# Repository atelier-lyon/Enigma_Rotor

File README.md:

# Enigma Rotor

## By Florian "FloRide" Reimat

## About

This repo is the Rotor panel PCB of the Enigma project

## Images:

### Schematic:

### PCB:

|               Front                |               Bottom               |
| :--------------------------------: | :--------------------------------: |
|  |  |

### 3D:

|                 Front                  |                Bottom                |
| :------------------------------------: | :----------------------------------: |
|    |  |
|                Tilted 1                |               Tilted 2               |
|  |   |

## Others:

- [Interactive BOM](Export/ibom/Engima_Rotor-ibom.html)
- [BOM](Export/bom/Engima_Rotor-bom.csv)
- [Cost](Export/cost/Engima_Rotor-kicost.xlsx)

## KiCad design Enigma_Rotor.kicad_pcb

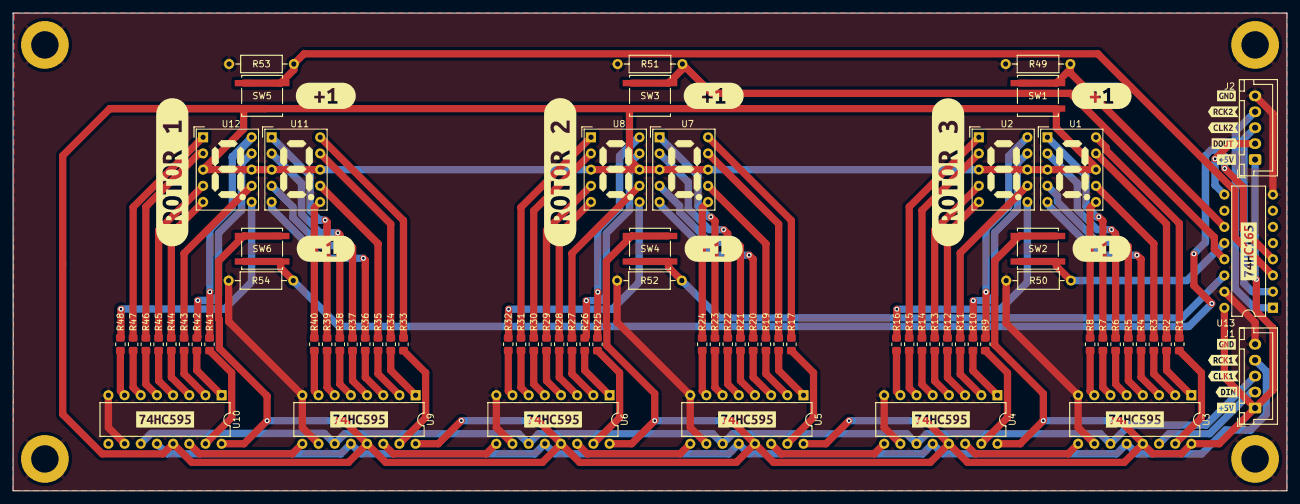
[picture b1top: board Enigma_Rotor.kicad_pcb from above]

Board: 2 copper layers, 200.0 x 75.0 mm, 105 parts (0 on the bottom side), 115 nets.

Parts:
H1, H2, H3, H4: MountingHole_Pad; MountingHole_4.3mm_M4_DIN965_Pad
J1, J2: Conn_01x05; JST_XH_B5B-XH-A_1x05_P2.50mm_Vertical
R1, R2, R3, R4, R5, R6, R7, R8, R9, R10, R11, R12, R13, R14, R15, R16, R17, R18, R19, R20, R21, R22, R23, R24, R25, R26, R27, R28, R29, R30, R31, R32, R33, R34, R35, R36, R37, R38, R39, R40, R41, R42, R43, R44, R45, R46, R47, R48: 155; R_0805_2012Metric_Pad1.20x1.40mm_HandSolder
R49, R50, R51, R52, R53, R54: 10k; R_Axial_DIN0207_L6.3mm_D2.5mm_P10.16mm_Horizontal
SW1, SW2, SW3, SW4, SW5, SW6: SW_Push_Dual; SW_Push_1P1T_NO_CK_KSC6xxJ
U1, U2, U7, U8, U11, U12: HDSP-561E
U3, U4, U5, U6, U9, U10: 74HC595; DIP-16_W7.62mm
U13: 74HC165; DIP-16_W7.62mm
kibuzzard-63728A6D: G***; kibuzzard-63728A6D
kibuzzard-63728A42: G***; kibuzzard-63728A42
kibuzzard-63728A55: G***; kibuzzard-63728A55
kibuzzard-63728A60: G***; kibuzzard-63728A60
kibuzzard-63728A71: G***; kibuzzard-63728A71
kibuzzard-637289C5: G***; kibuzzard-637289C5
kibuzzard-637289FA, kibuzzard-637289FA#2: G***; kibuzzard-637289FA
kibuzzard-6372869D, kibuzzard-6372869D#2, kibuzzard-6372869D#3: G***; kibuzzard-6372869D
kibuzzard-6372875B: G***; kibuzzard-6372875B
kibuzzard-6372894E: G***; kibuzzard-6372894E
kibuzzard-63728640, kibuzzard-63728640#2, kibuzzard-63728640#3: G***; kibuzzard-63728640
kibuzzard-63728741, kibuzzard-63728741#2, kibuzzard-63728741#3, kibuzzard-63728741#4, kibuzzard-63728741#5, kibuzzard-63728741#6: G***; kibuzzard-63728741
kibuzzard-63728829: G***; kibuzzard-63728829
kibuzzard-63728953: G***; kibuzzard-63728953
kibuzzard-63728972, kibuzzard-63728972#2: G***; kibuzzard-63728972

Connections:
+5V: J1.1, J2.1, SW1.1, SW2.1, SW3.1, SW4.1, SW5.1, SW6.1, U1.3 (CA), U1.8 (CA), U2.3 (CA), U2.8 (CA), U3.13 (~OE), U3.16 (VCC), U4.13 (~OE), U4.16 (VCC), U5.13 (~OE), U5.16 (VCC), U6.13 (~OE), U6.16 (VCC), U7.3 (CA), U7.8 (CA), U8.3 (CA), U8.8 (CA), U9.13 (~OE), U9.16 (VCC), U10.13 (~OE), U10.16 (VCC), U11.3 (CA), U11.8 (CA), U12.3 (CA), U12.8 (CA), U13.16 (VCC)
/ROTOR_1_DOWN: R50.1, SW2.2, U13.12 (D1)
/ROTOR_1_UP: R49.1, SW1.2, U13.11 (D0)
/ROTOR_2_DOWN: R52.1, SW4.2, U13.14 (D3)
/ROTOR_2_UP: R51.1, SW3.2, U13.13 (D2)
/ROTOR_3_DOWN: R54.1, SW6.2, U13.4 (D5)
/ROTOR_3_UP: R53.1, SW5.2, U13.3 (D4)
GND: H1.1, H2.1, H3.1, H4.1, J1.5, J2.5, R49.2, R50.2, R51.2, R52.2, R53.2, R54.2, U3.8 (GND), U3.10 (~SRCLR), U4.8 (GND), U4.10 (~SRCLR), U5.8 (GND), U5.10 (~SRCLR), U6.8 (GND), U6.10 (~SRCLR), U9.8 (GND), U9.10 (~SRCLR), U10.8 (GND), U10.10 (~SRCLR), U13.8 (GND), U13.15 (~CE)
unnamed: R1.2, U1.10 (A)
unnamed: R2.2, U1.9 (B)
unnamed: R3.2, U1.7 (C)
unnamed: R4.2, U1.5 (D)
unnamed: R8.2, U1.6 (DP)
unnamed: R5.2, U1.4 (E)
unnamed: R6.2, U1.2 (F)
unnamed: R7.2, U1.1 (G)
unnamed: R9.2, U2.10 (A)
unnamed: R10.2, U2.9 (B)
unnamed: R11.2, U2.7 (C)
unnamed: R12.2, U2.5 (D)
unnamed: R16.2, U2.6 (DP)
unnamed: R13.2, U2.4 (E)
unnamed: R14.2, U2.2 (F)
unnamed: R15.2, U2.1 (G)
unnamed: R1.1, U3.15 (QA)
unnamed: R2.1, U3.1 (QB)
unnamed: R3.1, U3.2 (QC)
unnamed: R4.1, U3.3 (QD)
unnamed: R5.1, U3.4 (QE)
unnamed: R6.1, U3.5 (QF)
unnamed: R7.1, U3.6 (QG)
unnamed: U3.9 (QH'), U4.14 (SER)
unnamed: R8.1, U3.7 (QH)
unnamed: R9.1, U4.15 (QA)
unnamed: R10.1, U4.1 (QB)
unnamed: R11.1, U4.2 (QC)
unnamed: R12.1, U4.3 (QD)
unnamed: R13.1, U4.4 (QE)
unnamed: R14.1, U4.5 (QF)
unnamed: R15.1, U4.6 (QG)
unnamed: U4.9 (QH'), U5.14 (SER)
unnamed: R16.1, U4.7 (QH)
unnamed: R17.1, U5.15 (QA)
unnamed: R18.1, U5.1 (QB)
unnamed: R19.1, U5.2 (QC)
unnamed: R20.1, U5.3 (QD)
unnamed: R21.1, U5.4 (QE)
unnamed: R22.1, U5.5 (QF)
unnamed: R23.1, U5.6 (QG)
unnamed: U5.9 (QH'), U6.14 (SER)
unnamed: R24.1, U5.7 (QH)
unnamed: R25.1, U6.15 (QA)
unnamed: R26.1, U6.1 (QB)
unnamed: R27.1, U6.2 (QC)
unnamed: R28.1, U6.3 (QD)
unnamed: R29.1, U6.4 (QE)
unnamed: R30.1, U6.5 (QF)
unnamed: R31.1, U6.6 (QG)
unnamed: U6.9 (QH'), U9.14 (SER)
unnamed: R32.1, U6.7 (QH)
unnamed: R17.2, U7.10 (A)
unnamed: R18.2, U7.9 (B)
unnamed: R19.2, U7.7 (C)
unnamed: R20.2, U7.5 (D)
unnamed: R24.2, U7.6 (DP)
unnamed: R21.2, U7.4 (E)
unnamed: R22.2, U7.2 (F)
unnamed: R23.2, U7.1 (G)
unnamed: R25.2, U8.10 (A)
unnamed: R26.2, U8.9 (B)
unnamed: R27.2, U8.7 (C)
unnamed: R28.2, U8.5 (D)
unnamed: R32.2, U8.6 (DP)
unnamed: R29.2, U8.4 (E)
unnamed: R30.2, U8.2 (F)
unnamed: R31.2, U8.1 (G)
unnamed: R33.1, U9.15 (QA)
unnamed: R34.1, U9.1 (QB)
unnamed: R35.1, U9.2 (QC)
unnamed: R36.1, U9.3 (QD)
unnamed: R37.1, U9.4 (QE)
unnamed: R38.1, U9.5 (QF)
unnamed: R39.1, U9.6 (QG)
unnamed: R40.1, U9.7 (QH)
unnamed: R41.1, U10.15 (QA)
unnamed: R42.1, U10.1 (QB)
unnamed: R43.1, U10.2 (QC)
unnamed: R44.1, U10.3 (QD)
unnamed: R45.1, U10.4 (QE)
unnamed: R46.1, U10.5 (QF)
unnamed: R47.1, U10.6 (QG)
unnamed: R48.1, U10.7 (QH)
unnamed: U9.9 (QH'), U10.14 (SER)
unnamed: R33.2, U11.10 (A)
unnamed: R34.2, U11.9 (B)
unnamed: R35.2, U11.7 (C)
unnamed: R36.2, U11.5 (D)
unnamed: R40.2, U11.6 (DP)
unnamed: R37.2, U11.4 (E)
unnamed: R38.2, U11.2 (F)
unnamed: R39.2, U11.1 (G)
unnamed: R41.2, U12.10 (A)
unnamed: R42.2, U12.9 (B)
unnamed: R43.2, U12.7 (C)
unnamed: R44.2, U12.5 (D)
unnamed: R48.2, U12.6 (DP)
unnamed: R45.2, U12.4 (E)
unnamed: R46.2, U12.2 (F)
unnamed: R47.2, U12.1 (G)
ROTOR_CLK: J1.3, U3.11 (SRCLK), U4.11 (SRCLK), U5.11 (SRCLK), U6.11 (SRCLK), U9.11 (SRCLK), U10.11 (SRCLK)
ROTOR_DIN: J1.2, U3.14 (SER)
ROTOR_RCK: J1.4, U3.12 (RCLK), U4.12 (RCLK), U5.12 (RCLK), U6.12 (RCLK), U9.12 (RCLK), U10.12 (RCLK)
ROT_IN_CLK: J2.3, U13.2 (CP)
ROT_IN_DOUT: J2.2, U13.9 (Q7)
ROT_IN_RCK: J2.4, U13.1 (~PL)

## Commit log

2022-11-15 [ROOT] Initial commit
2022-11-15 [ROOT] Add Kicad files
2022-11-15 [CI/CD] Add CI/CD + Kibot
